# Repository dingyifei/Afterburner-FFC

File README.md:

# Afterburner FFC
 FFC mod for the voron afterburner

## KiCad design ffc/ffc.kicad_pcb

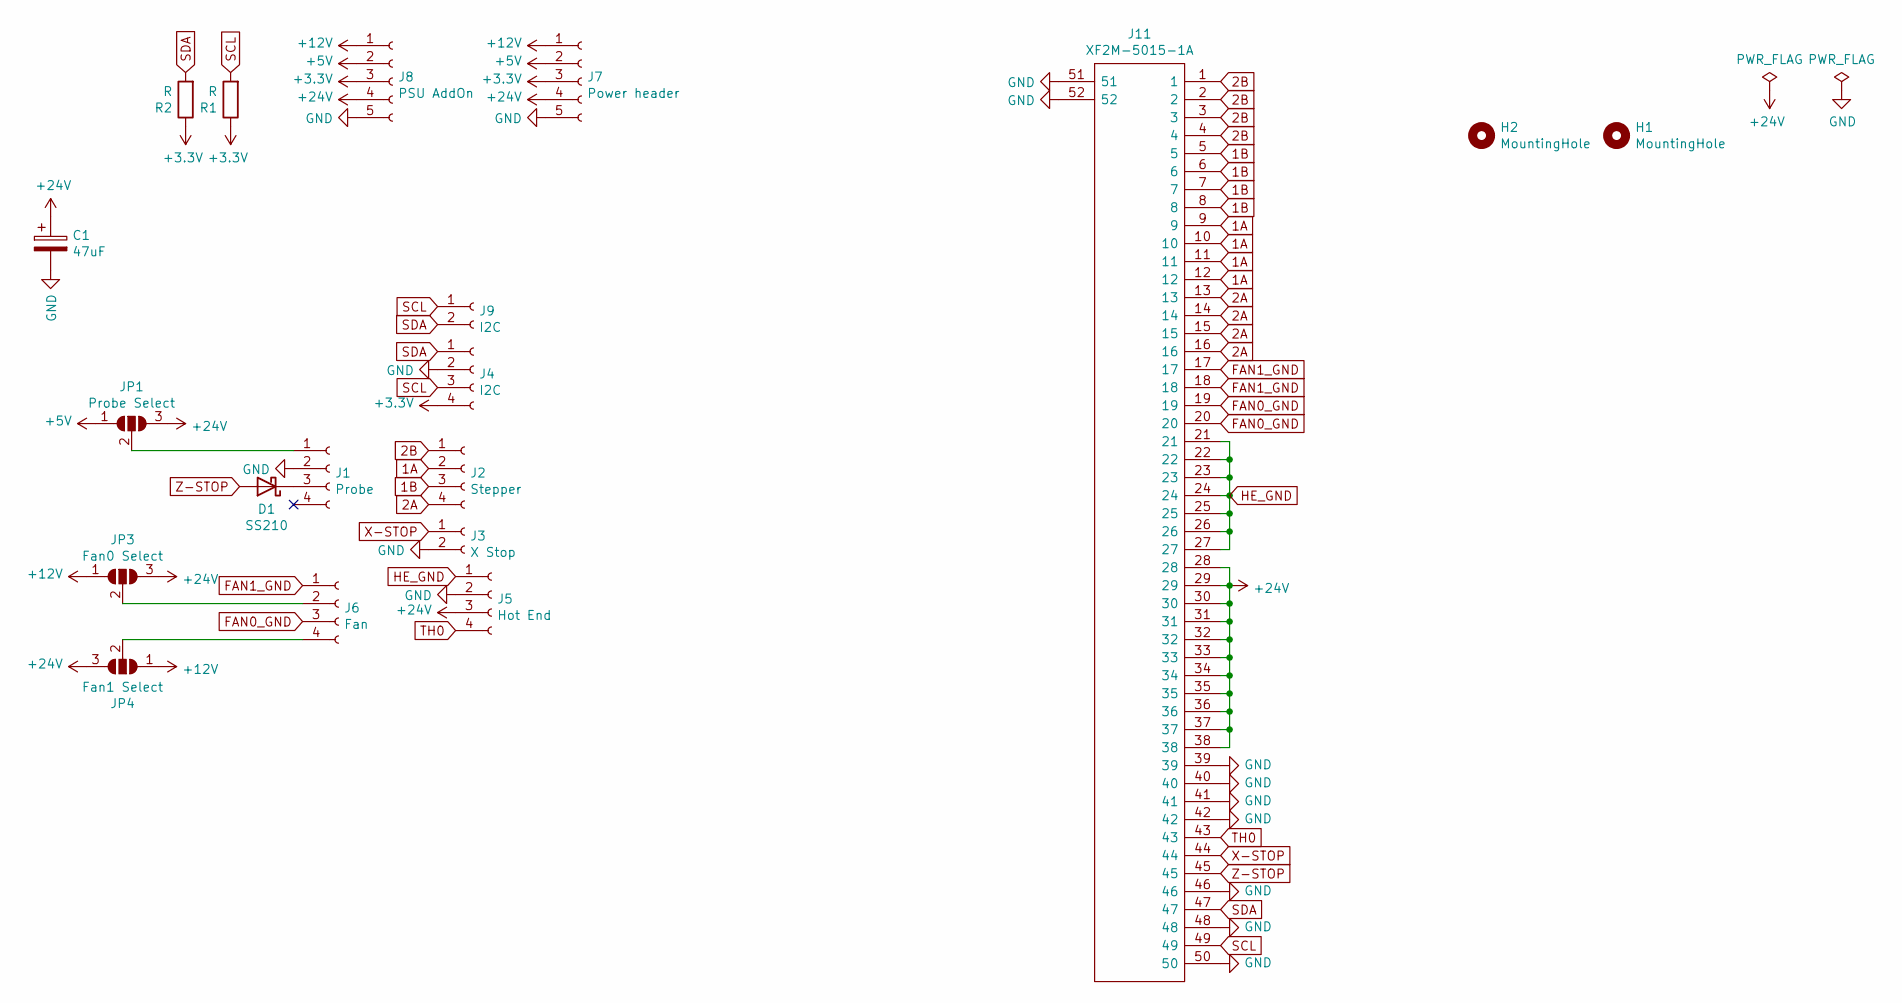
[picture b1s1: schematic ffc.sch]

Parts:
C1: 47uF; CP_EIA-7343-30_AVX-N_Pad2.25x2.55mm_HandSolder
D1: SS210; D_SMA
H1, H2: MountingHole; MountingHole_3.2mm_M3
J1: Probe; Molex_Micro-Fit_3.0_43045-0412_2x02_P3.00mm_Vertical
J2: Stepper; Molex_Micro-Fit_3.0_43045-0412_2x02_P3.00mm_Vertical
J3: X Stop; Molex_Micro-Fit_3.0_43045-0212_2x01_P3.00mm_Vertical
J4: I2C; Molex_Micro-Fit_3.0_43045-0412_2x02_P3.00mm_Vertical
J5: Hot End; Molex_Micro-Fit_3.0_43045-0412_2x02_P3.00mm_Vertical
J6: Fan; Molex_Micro-Fit_3.0_43045-0412_2x02_P3.00mm_Vertical
J7: Power header; PinSocket_1x05_P2.54mm_Vertical
J8: PSU AddOn; PinSocket_1x05_P2.54mm_Vertical
J9: I2C; PinSocket_1x02_P2.54mm_Vertical
J11: XF2M-5015-1A; XF2M50151A; Mouser Part Number 653-XF2M-5015-1A
JP1: Probe Select; SolderJumper-3_P1.3mm_Open_Pad1.0x1.5mm_NumberLabels
JP3: Fan0 Select; SolderJumper-3_P1.3mm_Open_Pad1.0x1.5mm_NumberLabels
JP4: Fan1 Select; SolderJumper-3_P1.3mm_Open_Pad1.0x1.5mm_NumberLabels
R1, R2: R; R_0402_1005Metric

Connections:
1A: J2.2, J11.9, J11.10, J11.11, J11.12
1B: J2.3, J11.5, J11.6, J11.7, J11.8
2A: J2.4, J11.13, J11.14, J11.15, J11.16
2B: J2.1, J11.1, J11.2, J11.3, J11.4
+3V3: J4.4, J7.3, J8.3, R1.1, R2.1
+5V: J7.2, J8.2, JP1.1 (A)
+12V: J7.1, J8.1, JP3.1 (A), JP4.1 (A)
+24V: C1.1, J5.3, J7.4, J8.4, J11.28, J11.29, J11.30, J11.31, J11.32, J11.33, J11.34, J11.35, J11.36, J11.37, J11.38, JP1.3 (B), JP3.3 (B), JP4.3 (B)
FAN0_GND: J6.3, J11.19, J11.20
FAN1_GND: J6.1, J11.17, J11.18
GND: C1.2, J1.2, J3.2, J4.2, J5.2, J7.5, J8.5, J11.39, J11.40, J11.41, J11.42, J11.46, J11.48, J11.50, J11.51, J11.52
HE_GND: J5.1, J11.21, J11.22, J11.23, J11.24, J11.25, J11.26, J11.27
unnamed: D1.1 (K), J1.3
unnamed: J1.1, JP1.2 (C)
unnamed: J6.2, JP3.2 (C)
unnamed: J6.4, JP4.2 (C)
SCL: J4.3, J9.1, J11.49, R1.2
SDA: J4.1, J9.2, J11.47, R2.2
TH0: J5.4, J11.43
X-STOP: J3.1, J11.44
Z-STOP: D1.2 (A), J11.45

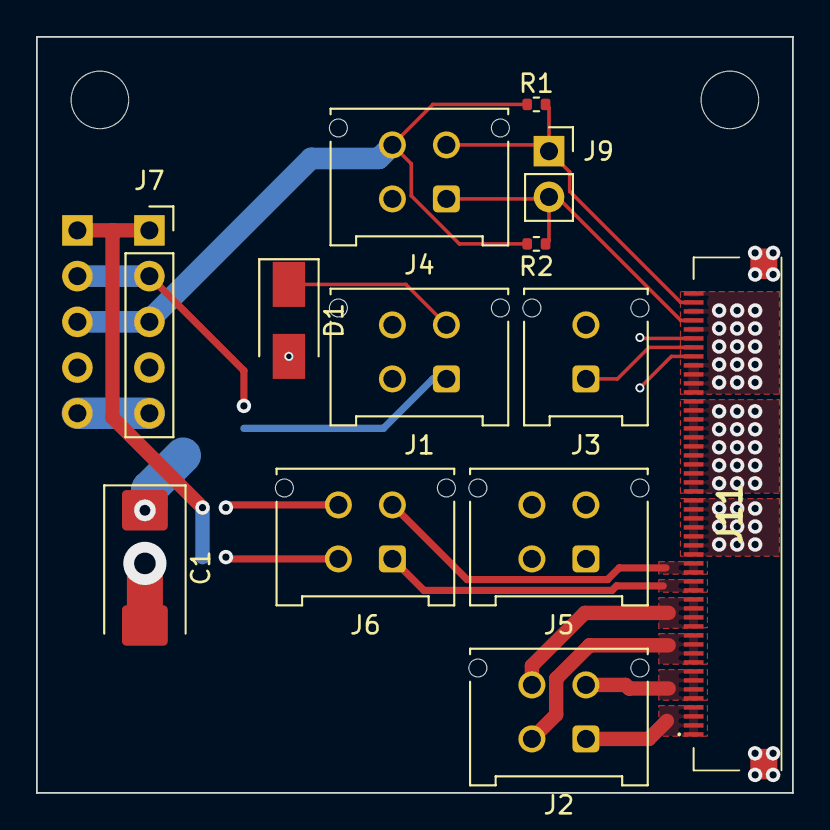
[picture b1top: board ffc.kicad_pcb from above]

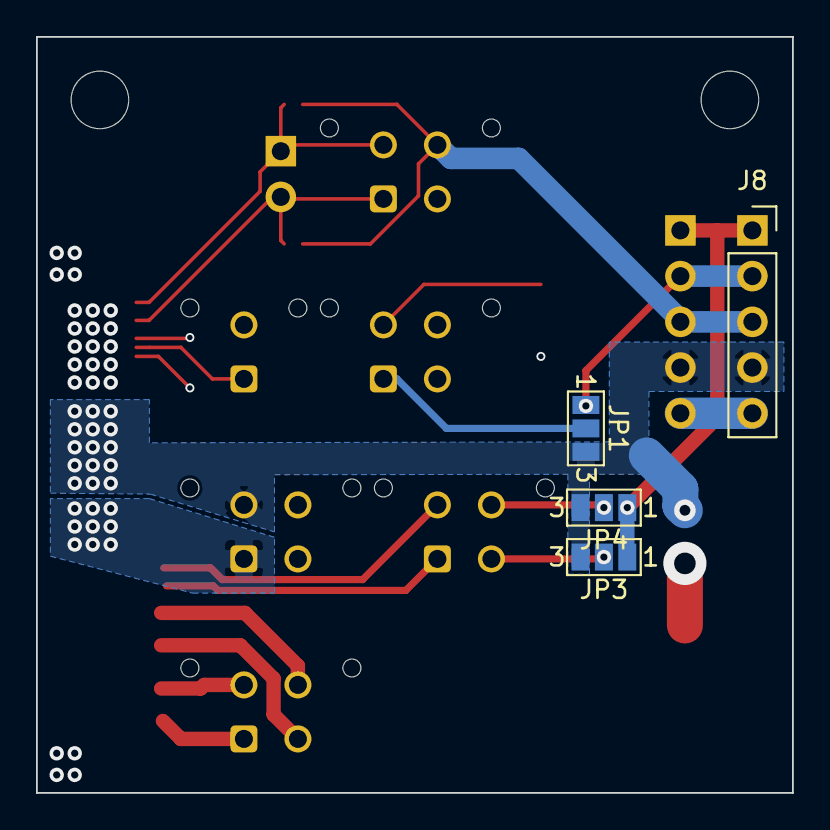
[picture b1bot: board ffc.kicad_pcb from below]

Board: 4 copper layers, 42.0 x 42.0 mm, 19 parts (4 on the bottom side), 21 nets.

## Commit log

2021-04-01 Afterburner end is 50% done
